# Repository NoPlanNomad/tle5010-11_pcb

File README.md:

# tle5010-11_pcb
 
mounting pcb for this gimbal: https://www.printables.com/model/565234-olukelo-gimbal-threaded-arm-and-sensor-mounting

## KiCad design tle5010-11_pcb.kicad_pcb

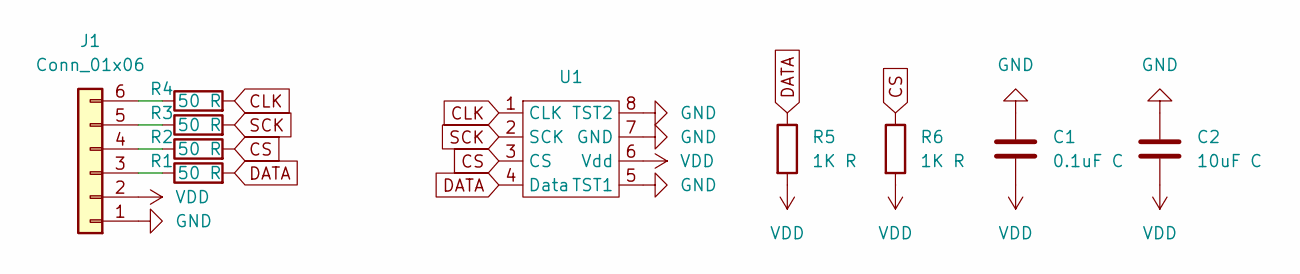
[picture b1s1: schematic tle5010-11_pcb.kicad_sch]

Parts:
C1: 0.1uF C; C_0805_2012Metric_Pad1.18x1.45mm_HandSolder
C2: 10uF C; C_0805_2012Metric_Pad1.18x1.45mm_HandSolder
J1: Conn_01x06; PinHeader_1x06_P2.54mm_Vertical
R1, R2, R3, R4: 50 R; R_0805_2012Metric_Pad1.20x1.40mm_HandSolder
R5, R6: 1K R; R_0805_2012Metric_Pad1.20x1.40mm_HandSolder
U1: SOIC-8_3.9x4.9mm_P1.27mm

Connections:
CLK: R4.2, U1.1 (CLK)
CS: R2.2, R6.1, U1.3 (CS)
DATA: R1.2, R5.1, U1.4 (Data)
GND: C1.2, C2.2, J1.1, U1.5 (TST1), U1.7 (GND), U1.8 (TST2)
unnamed: J1.3, R1.1
unnamed: J1.4, R2.1
unnamed: J1.5, R3.1
unnamed: J1.6, R4.1
SCK: R3.2, U1.2 (SCK)
VDD: C1.1, C2.1, J1.2, R5.2, R6.2, U1.6 (Vdd)

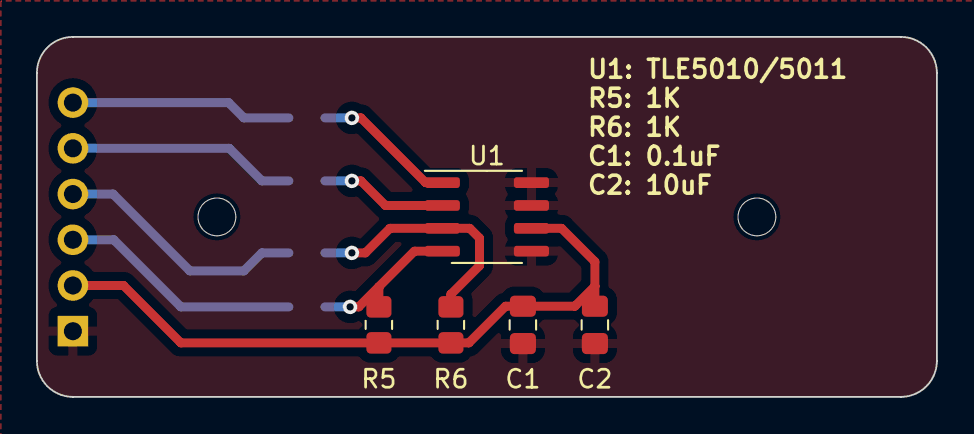
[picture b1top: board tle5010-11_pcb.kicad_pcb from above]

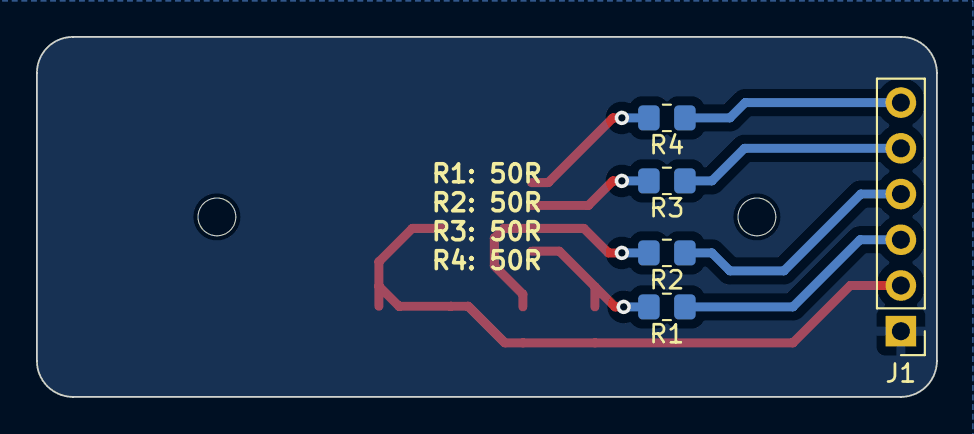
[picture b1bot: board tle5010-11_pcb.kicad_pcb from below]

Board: 2 copper layers, 50.0 x 20.0 mm, 10 parts (5 on the bottom side), 10 nets.

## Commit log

2023-09-05 finalised pcb
